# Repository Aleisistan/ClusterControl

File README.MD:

# ClusterControl

Aplicación web para administrar clusters y consultar telemetría de dispositivos
conectados por MQTT. Incluye una API, una interfaz web, PostgreSQL y un broker
MQTT.

## Requisitos

- Docker Desktop o Docker Engine con Docker Compose v2.
- Git.

No necesitas instalar Node.js ni Python para iniciar la aplicación con Docker.

## Desarrollo

1. Si todavía no tienes el archivo local de desarrollo, créalo desde la
   plantilla:

   ```powershell
   if (-not (Test-Path .env.development.local)) {
     Copy-Item .env.example .env.development.local
   }
   ```

   `.env.development.local` es local y no se sube a Git. El Compose de desarrollo
   usa credenciales de prueba `admin` / `admin123` y crea clusters de ejemplo.
   No sobrescribas un archivo local que ya tenga tu configuración. No expongas
   este entorno ni uses esas credenciales en producción. El broker de desarrollo
   permite conexiones MQTT anónimas; mantenlo en una red local de confianza.
   Como `.env.example` contiene valores de producción, en
   `.env.development.local` cambia `API_URL` por una dirección accesible desde
   el navegador. Con los puertos locales predeterminados, usa:

   ```dotenv
   API_URL=http://localhost:3000
   SOCKET_URL=
   ```

   Para habilitar el inicio de pruebas de resistencia desde el dashboard, agrega
   una clave interna aleatoria al archivo local (no la compartas ni la subas a
   Git). En PowerShell, si todavía no existe:

   ```powershell
   if (-not (Select-String -Path .env.development.local -Pattern '^INDUSTRIAL_TEST_CONTROL_TOKEN=' -Quiet)) {
     $token = python -c "import secrets; print(secrets.token_urlsafe(48))"
     Add-Content .env.development.local "INDUSTRIAL_TEST_CONTROL_TOKEN=$token"
   }
   ```

   El backend y el contenedor de pruebas usan la misma clave; el servicio de
   control no publica ningún puerto en el host.

   Si accedes desde otro equipo, reemplaza `localhost` por la IP o el DNS del
   servidor. `SOCKET_URL` vacío hace que Socket.IO use ese mismo host. Este es
   el único archivo de entorno de desarrollo; el backend también lo usa al
   ejecutarse directamente.

2. Desde la raíz del repositorio, inicia los servicios:

   ```powershell
   docker compose --env-file .env.development.local -f docker-compose.dev.yml up --build -d
   ```

3. Abre <http://localhost:4200> e inicia sesión. Otros accesos locales:

   - API: <http://localhost:3000>
   - pgAdmin: <http://localhost:5050> (por defecto, `admin@example.com` /
     `development-only-change-me`)
   - MQTT: `localhost:1883`

El código fuente del backend y frontend está montado desde el host. Al guardar
cambios, Nest reinicia la API y Angular actualiza la web automáticamente; no
hace falta reconstruir las imágenes para cambios de código. Los cambios en
dependencias o Dockerfiles sí requieren reconstrucción:

```powershell
docker compose --env-file .env.development.local -f docker-compose.dev.yml up --build -d backend frontend
```

El entorno incluye PostgreSQL, Mosquitto, el simulador MQTT y un contenedor de
pruebas industriales que expone el control de ejecución solo en la red interna
de Docker. Desde el dashboard, un administrador puede iniciar pruebas de
resistencia de 24 a 8760 horas; el runner continúa aunque se cierre el navegador. El simulador
publica telemetría de ejemplo para China y Alemania; el dashboard de desarrollo
muestra esas lecturas junto con las de dispositivos reales, pero excluye los
datos de pruebas industriales. Si cambias la configuración del clima, agrega tu
`OPENWEATHER_API_KEY` a `.env.development.local` y recrea el backend:

```powershell
docker compose --env-file .env.development.local -f docker-compose.dev.yml up -d --force-recreate backend
```

Sin una clave válida de OpenWeather, el panel del clima no está disponible. El
simulador no necesita configuración adicional. Detenlo si vas a probar hardware
real sin lecturas sintéticas:

```powershell
docker compose --env-file .env.development.local -f docker-compose.dev.yml stop simulator
```

Para ver logs o detener el entorno:

```powershell
docker compose --env-file .env.development.local -f docker-compose.dev.yml logs -f
docker compose --env-file .env.development.local -f docker-compose.dev.yml down
```

Los datos se conservan al detener los servicios. `down -v` también elimina los
volúmenes de desarrollo y la base de datos.

## Producción

1. En la primera instalación, copia `.env.example` como `.env` en el servidor.
   No reemplaces un `.env` que ya contenga la configuración de producción.
2. Reemplaza todos los valores `REEMPLAZAR_*` por valores seguros. Configura
   `API_URL=/api` (para que Angular use el proxy Nginx) y, si el backend no es
   accesible como `backend` en la red de Compose, ajusta `BACKEND_URL`.
   Configura contraseñas únicas y asegúrate de que `POSTGRES_PASSWORD` y
   `DB_PASSWORD` coincidan.
3. Inicia o actualiza los servicios:

   ```bash
   docker compose --env-file .env -f docker-compose.yml up -d
   ```

   Si las imágenes son privadas, inicia sesión con `docker login ghcr.io`.
   El backend aplica las migraciones al iniciar; antes de actualizar una
   instalación existente, realiza una copia de seguridad de PostgreSQL.

El workflow de CI ejecuta pruebas en pull requests y publica las imágenes en
pushes a `main` o a etiquetas `v*` ([workflow](./.github/workflows/ci-cd.yml)).
Publica etiquetas `latest`, de commit y de versión para los tags `v*`. Por
defecto Compose usa `latest`; para fijar una versión, configura
`BACKEND_IMAGE` y `FRONTEND_IMAGE` en `.env` con sus etiquetas, por ejemplo
`ghcr.io/aleisistan/clustercontrol-backend:v1.0.0`. Compose consulta las
imágenes en cada `up`. Producción no monta el código fuente ni lo recarga
automáticamente.

La aplicación queda disponible en el puerto `FRONTEND_HOST_PORT` (80 por
defecto). Nginx sirve el frontend y pasa `/api` y Socket.IO al backend por la
red interna. Producción no incluye pgAdmin, simulador, clusters de muestra ni
runner de pruebas industriales. La sección de estado de pruebas industriales y
sus consultas periódicas solo están habilitadas en desarrollo. El administrador
inicial se define mediante `INITIAL_ADMIN_USERNAME` y
`INITIAL_ADMIN_PASSWORD`.

El Compose de producción usa un listener MQTT autenticado. Antes de iniciar los
servicios, copia `mosquitto/config/aclfile.example` como `aclfile` en el
servidor, crea el archivo de contraseñas del broker y configura las credenciales
del backend en `.env`. El `aclfile` operativo y `password_file` son locales y
están excluidos de Git. Antes de iniciar el broker, asígnalos al usuario
`mosquitto` y restringe sus permisos según la
[guía de conexión](./docs/conectar-dispositivo-mqtt.md). Si cambias `MQTT_USER`
o el usuario del dispositivo, actualiza también los nombres en el `aclfile`
operativo y al generar `password_file`; la guía de conexión explica cómo
preparar el servidor, el firewall y las placas.

## Clusters, dispositivos y cámaras

Los administradores crean clusters desde **Clusters**. El alta registra el
cluster y asigna su `deviceId`; no descubre ni conecta una placa automáticamente.
Para emparejar el dispositivo, configura ese identificador y el broker MQTT en
su firmware, y verifica que llegue telemetría. Consulta la
[guía de conexión de dispositivos](./docs/conectar-dispositivo-mqtt.md). Los
clusters de demostración se crean solo en desarrollo.

En el mismo menú se pueden asociar hasta dos cámaras a cada cluster, con nombre
y dirección IP o URL completa de stream. Cada registro ocupa el slot 1 o 2;
dos cámaras pueden compartir una IP si usan puertos o rutas distintas, por
ejemplo `http://192.168.2.228:8081/stream` y
`http://192.168.2.228:8082/stream`. Al actualizar una base existente, el
backend aplica las migraciones necesarias para permitir ambas cámaras por
cluster.

Para streams MJPEG con host IP, el backend comparte una conexión de cámara
entre los dashboards de esa instancia; las URL HLS con host IP se retransmiten
por proxy. Las URL con nombre de dominio se abren desde su origen y no usan el
relay compartido. No configures la cámara en una variable de entorno. Consulta
la [guía de cámaras](./docs/camera-stream-multicliente.md). Como alternativa,
un dispositivo que publique la IP de su cámara por MQTT puede crear o
actualizar ese registro.

Las aperturas de puerta detectadas en telemetría real pueden guardar una
captura en PostgreSQL. El dashboard muestra en línea las cuatro capturas más
recientes del período seleccionado y agrupa las anteriores en un desplegable;
consulta la [guía de cámaras](./docs/camera-stream-multicliente.md) para los
detalles.

## Hardware

Los esquemas y la placa están en [hardware/esp32/KiCad](./hardware/esp32/KiCad/)
y se describen en su [README](./hardware/esp32/KiCad/readme.md). El pinout,
los umbrales y la configuración del ESP32 están en la
[guía del firmware](./firmware/ClusterControl_ESP32/README.md).

## Pruebas

Para instalar dependencias, compilar y ejecutar pruebas unitarias, sigue los
README de [backend](./backend/README.md) y [frontend](./frontend/README.md).
Las pruebas industriales requieren el entorno de desarrollo; consulta su
[guía](./tests-industriales/README.md).

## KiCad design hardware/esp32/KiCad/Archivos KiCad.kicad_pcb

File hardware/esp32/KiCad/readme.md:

# Diseño de hardware ESP32

Esta carpeta contiene el proyecto electrónico de ClusterControl. Para
consultar o modificar el diseño, abre `Archivos KiCad.kicad_pro` en KiCad.

## Archivos principales

- `Archivos KiCad.kicad_sch`: esquema eléctrico.
- `Archivos KiCad.kicad_pcb`: diseño de la placa.
- `Archivos KiCad.net`: netlist exportada.
- `Archivos KiCad-PTH.drl` y `Archivos KiCad-NPTH.drl`: archivos de taladrado
  para agujeros metalizados y no metalizados.
- `DRC.rpt`: reporte de reglas de diseño; revísalo antes de fabricar.

La carpeta también incluye PDFs e imágenes de referencia (`DIAGRAMA.pdf`,
`PLACA.pdf` y vistas de capas). Son exportaciones, no reemplazan los archivos
fuente de KiCad.

Antes de fabricar, abre el diseño fuente, ejecuta las comprobaciones DRC y
genera los archivos de fabricación requeridos por el fabricante. Los PDFs y
taladros incluidos no constituyen por sí solos un paquete completo de
fabricación. Para conocer el pinout del firmware, consulta el
[README del ESP32](../../../firmware/ClusterControl_ESP32/README.md).

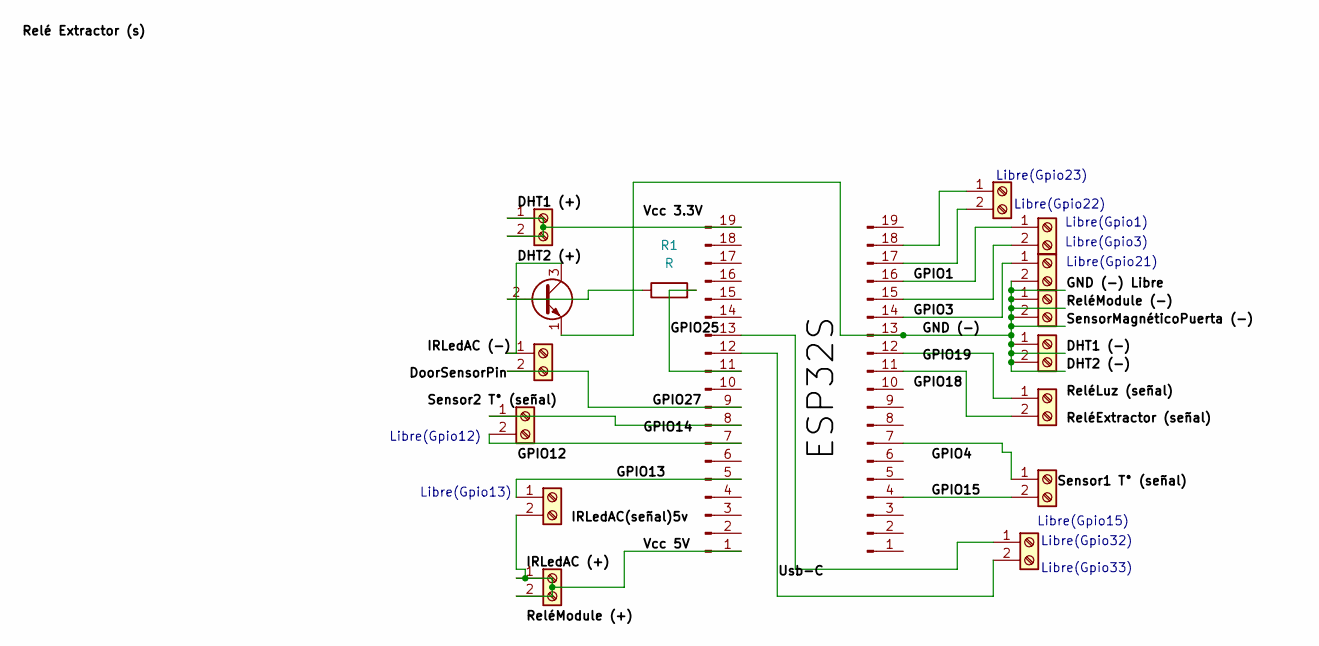
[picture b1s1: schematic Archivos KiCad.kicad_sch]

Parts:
J2, J19: Conn_01x19_Pin; PinSocket_1x19_P2.54mm_Vertical
J3, J4, J5, J6, J7, J8, J9, J10, J11, J12, J13, J14, J15: Screw_Terminal_01x02; TerminalBlock_Phoenix_MKDS-1,5-2-5.08_1x02_P5.08mm_Horizont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
Q1: Q_NPN_EBC; TO-92_Inline_Wide
R1: R; R_Axial_DIN0207_L6.3mm_D2.5mm_P7.62mm_Horizontal

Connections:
/DHT1 (-): J2.13 (Pin_7), J7.1, J7.2, J8.2, J10.1, J10.2, Q1.1 (E)
/DHT2 (+): J12.1, Q1.3 (C)
/GPIO1: J2.16 (Pin_4), J13.1
/GPIO3: J2.14 (Pin_6), J8.1
/GPIO13: J4.1, J19.5 (Pin_15)
/GPIO15: J2.4 (Pin_16), J6.2
/GPIO25: J19.11 (Pin_9), R1.2
/GPIO27: J12.2, J19.9 (Pin_11)
/IRLedAC (+): J4.2, J5.1, J5.2, J19.1 (Pin_19)
/Usb-C: J15.2, J19.12 (Pin_8)
unnamed: J2.7 (Pin_13), J6.1
unnamed: J2.12 (Pin_8), J11.1
unnamed: J2.11 (Pin_9), J11.2
unnamed: J2.15 (Pin_5), J13.2
unnamed: J2.18 (Pin_2), J14.1
unnamed: J2.17 (Pin_3), J14.2
unnamed: J15.1, J19.13 (Pin_7)
unnamed: J3.1, J3.2, J19.19 (Pin_1)
unnamed: J9.1, J19.8 (Pin_12)
unnamed: J9.2, J19.7 (Pin_13)
unnamed: Q1.2 (B), R1.1

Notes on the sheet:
Libre(Gpio1)
Libre(Gpio33)
Libre(Gpio15)
Libre(Gpio12)
Libre(Gpio32)
Libre(Gpio21)
Libre(Gpio13)
Libre(Gpio3)
Libre(Gpio23)
Libre(Gpio22)

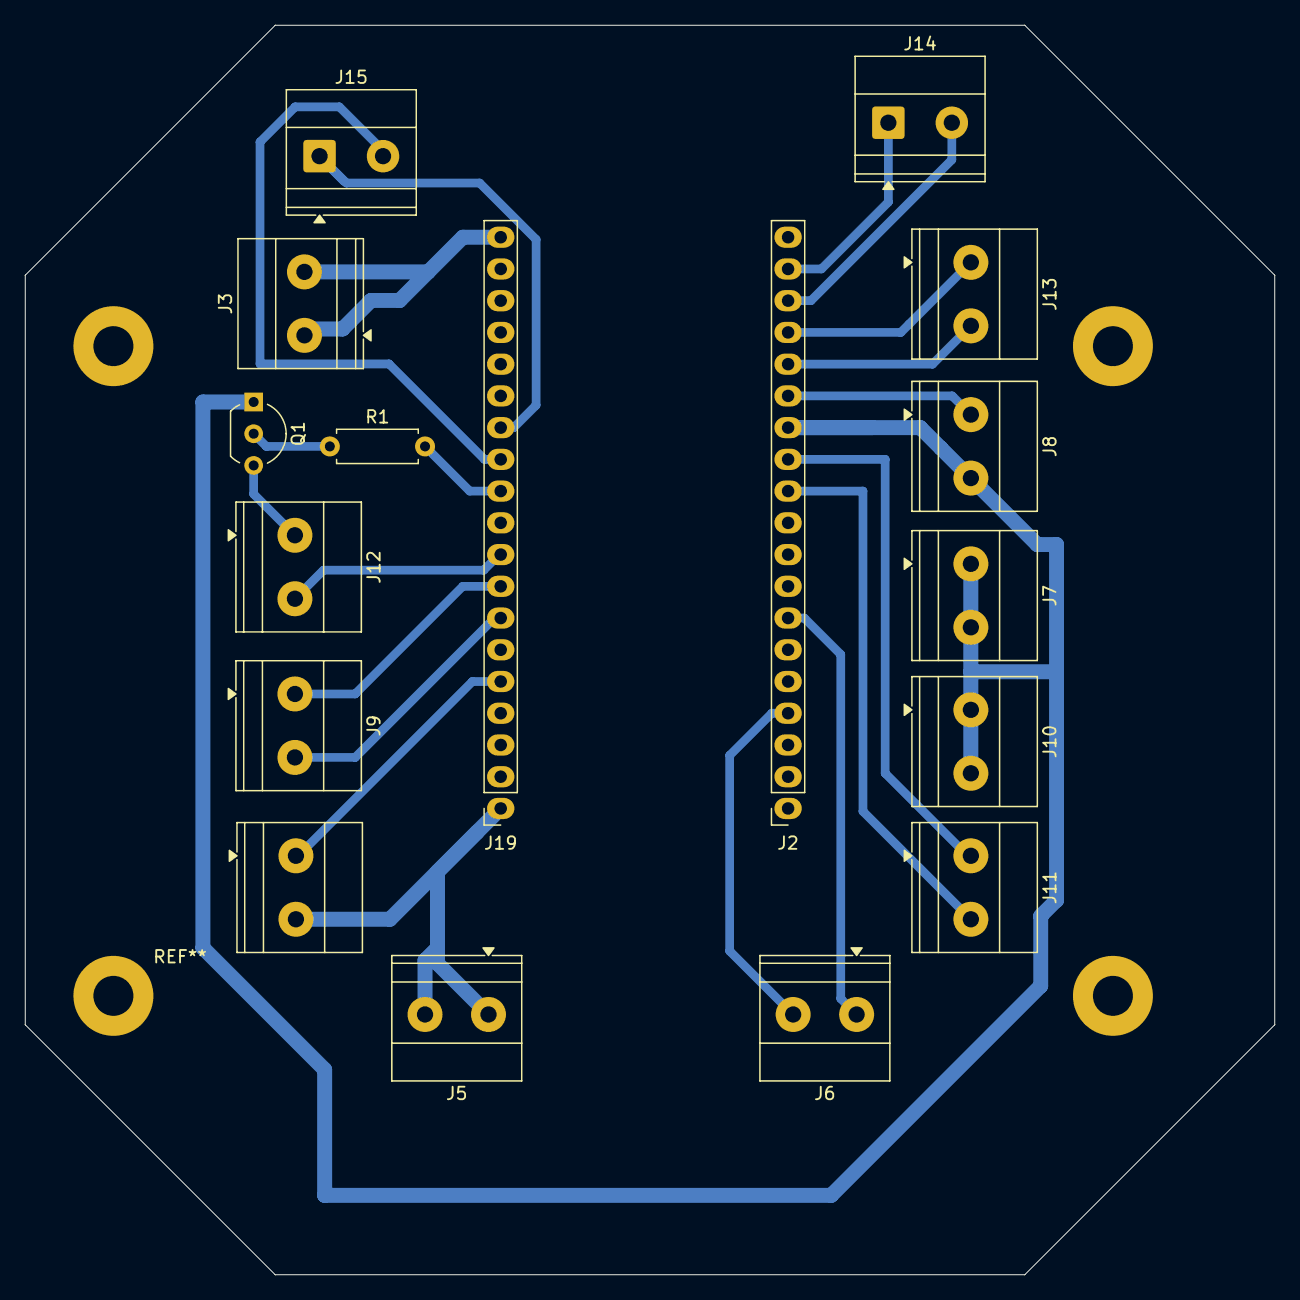
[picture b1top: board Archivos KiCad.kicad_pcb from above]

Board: 2 copper layers, 100.0 x 100.0 mm, 17 parts (0 on the bottom side), 21 nets.
